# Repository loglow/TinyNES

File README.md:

# TinyNES
Classic NES games on open source hardware that fits in the palm of your hand

This work is licensed under a [Creative Commons Attribution-ShareAlike 4.0 International License](http://creativecommons.org/licenses/by-sa/4.0/).

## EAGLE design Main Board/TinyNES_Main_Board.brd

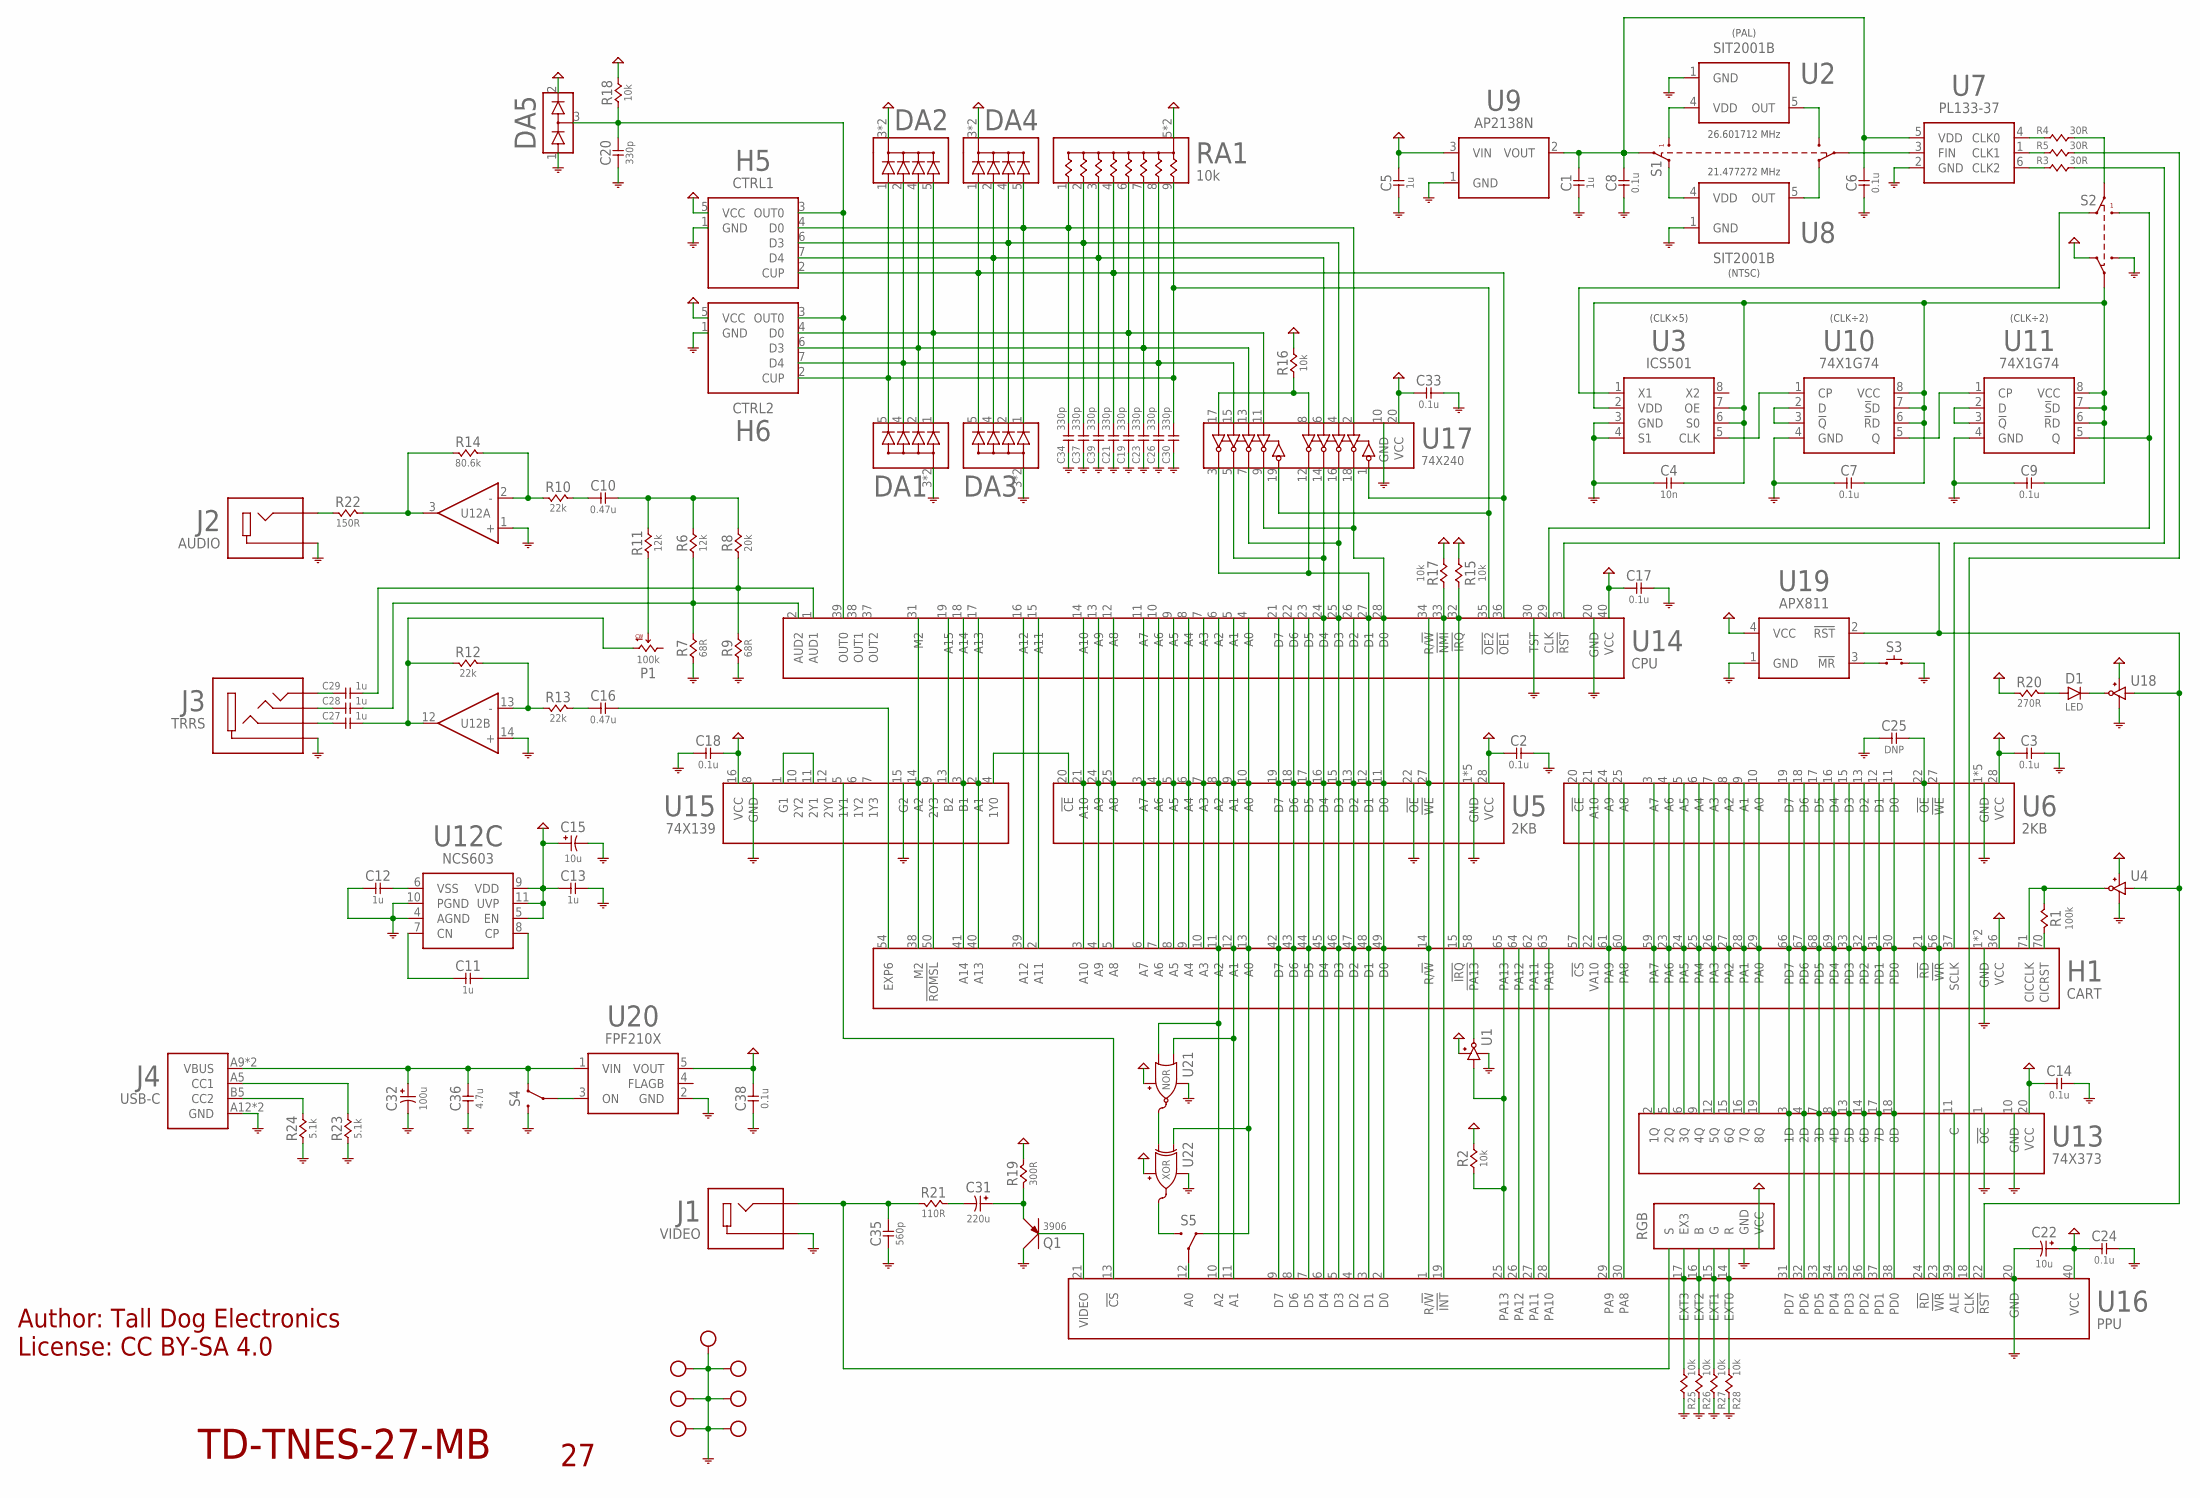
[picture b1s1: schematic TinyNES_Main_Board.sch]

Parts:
C1, C5, C11, C12, C13: 1u; 0805-NP
C2, C3, C6, C7, C8, C9, C14, C17, C18, C24, C33, C38: 0.1u; 0805-NP
C4: 10n; 0805-NP
C10, C16: 0.47u; 1206-NP
C15: 10u; ECAP-B
C19, C20, C21, C23, C26, C30, C34, C37, C39: 330p; 0805-NP
C22: 10u; 1206-P
C25: DNP; 0805-NP
C27, C28, C29: 1u; 1210-NP
C31: 220u; ECAP-E
C32: 100u; ECAP-D
C35: 560p; 0805-NP
C36: 4.7u; 0805-NP
D1: LED; LED-5MM
DA1, DA3: DA4-CA-SOT-363; SOT-363-NP
DA2, DA4: DA4-CK-SOT-363; SOT-363-NP
DA5: DA2-S; SOT-23-3
H1: CART; CART-72-2.50-CONN-VERT
H5: CTRL1; JST-PH-7
H6: CTRL2; JST-PH-7
HOLE1, HOLE2, HOLE3, HOLE4, HOLE5, HOLE6, HOLE7: HOLE-M2.5
J1: VIDEO; RCJ
J2: AUDIO; RCJ
J3: TRRS; SJ-43514
J4: USB-C; USB4125
P1: 100k; POT-3361
Q1: 3906; SOT-23-3
R1: 100k; 0805-NP
R2, R15, R16, R17, R18: 10k; 0805-NP
R3, R4, R5: 30R; 0805-NP
R6, R11: 12k; 0805-NP
R7, R9: 68R; 0805-NP
R8: 20k; 0805-NP
R10, R12, R13: 22k; 0805-NP
R14: 80.6k; 0805-NP
R19: 300R; 0805-NP
R20: 270R; 0805-NP
R21: 110R; 0805-NP
R22: 150R; 0805-NP
R23, R24: 5.1k; 0805-NP
R25, R26, R27, R28: 10k; 0603-NP
RA1: 10k; EXBA10P
RGB: RGB-TOP
S1: DPDT-LONG; JS202011J
S2: DPDT; JS202011J
S3: SWITCH; TL1105
S4: SPDT-EG1213; EG1213
S5: SPDT-CUS-12TB; CUS-12TB
U1, U4, U18: BUFFER; SOT-23-5
U2, U8: SIT2001B; SOT-23-5
U3: ICS501; SOIC-8
U5, U6: 2KB; SOIC-28
U7: PL133-37; SOT-23-6
U9: AP2138N; SOT-23-3
U10, U11: 74X1G74; TSSOP-8
U12: NCS603; TSSOP-14
U13: 74X373; SOIC-20
U14: CPU; DIP-40
U15: 74X139; SOIC-16
U16: PPU; DIP-40
U17: 74X240; SOIC-20
U19: APX811; SOT-143
U20: FPF210X; SOT-23-5
U21: NOR; SOT-23-5
U22: XOR; SOT-23-5

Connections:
1Y0-!CS: U5.20 (!CE), U15.4 (1Y0)
3V3: C1.1, C6.1, C8.1, S1.BCOM (2), U7.5 (VDD), U9.2 (VOUT)
!IRQ: H1.15 (!IRQ), R15.1, U14.32 (!IRQ)
!NMI: R17.1, U14.33 (!NMI), U16.19 (!INT)
!OE1: C21.2, DA3.5 (4), DA4.1, H5.2 (CUP), RA1.4, U14.36 (!OE1), U17.1 (1!OE)
!OE2: C30.2, DA1.5 (4), DA2.1, H6.2 (CUP), RA1.9 (8), U14.35 (!OE2), U17.19 (2!OE)
!PA13: H1.58 (!PA13), U1.4 (Y)
!ROMSEL: H1.50 (!ROMSL), U15.9 (2Y3)
A0: H1.13 (A0), S5.1, U5.10 (A0), U14.4 (A0), U22.1 (B)
A0-NOR: U21.4 (Y), U22.2 (A)
A0-PPU: S5.2, U16.12 (A0)
A0-XOR: S5.3, U22.4 (Y)
A1: H1.12 (A1), U5.9 (A1), U14.5 (A1), U16.11 (A1), U21.1 (B)
A2: H1.11 (A2), U5.8 (A2), U14.6 (A2), U16.10 (A2), U21.2 (A)
A3: H1.10 (A3), U5.7 (A3), U14.7 (A3)
A4: H1.9 (A4), U5.6 (A4), U14.8 (A4)
A5: H1.8 (A5), U5.5 (A5), U14.9 (A5)
A6: H1.7 (A6), U5.4 (A6), U14.10 (A6)
A7: H1.6 (A7), U5.3 (A7), U14.11 (A7)
A8: H1.5 (A8), U5.25 (A8), U14.12 (A8)
A9: H1.4 (A9), U5.24 (A9), U14.13 (A9)
A10: H1.3 (A10), U5.21 (A10), U14.14 (A10)
A11: H1.2 (A11), U14.15 (A11)
A12: H1.39 (A12), U14.16 (A12)
A13: H1.40 (A13), U14.17 (A13), U15.2 (A1)
A14: H1.41 (A14), U14.18 (A14), U15.3 (B1)
A15: U14.19 (A15), U15.13 (B2)
ALE: U13.11 (C), U16.39 (ALE)
AUDIO1-AC: C29.2, J3.2 (T)
AUDIO1-DC: C29.1, R8.1, R9.2, U14.1 (AUD1)
AUDIO2-AC: C28.2, J3.3 (RT)
AUDIO2-DC: C28.1, R6.1, R7.2, U14.2 (AUD2)
AUDIO-MIX: C10.2, R6.2, R8.2, R11.2
AUDIO-MIX-1: C10.1, R10.1
AUDIO-MIX-2: R10.2, R14.1, U12.2 (-)
AUDIO-MIX-AC: J2.2B (T), J2.2T (T), R22.2
AUDIO-MIX-DC: R14.2, R22.1, U12.3 (OUT)
CARTCLK: H1.37 (SCLK), R3.1
CC1: J4.A5 (CC1), R23.2
CC2: J4.B5 (CC2), R24.2
CIC: H1.71 (CICCLK), R1.2, U4.4 (Y)
CICRST: H1.70 (CICRST), R1.1
CLK0: R4.2, U7.4 (CLK0)
CLK1: R5.2, U7.1 (CLK1)
CLK2: R3.2, U7.6 (CLK2)
CLK5X: U3.5 (CLK), U10.1 (CP)
CLK5X/2: U10.5 (Q), U11.1 (CP)
CLK-FIN: S1.ACOM (5), U7.3 (FIN)
CLK-NTSC: S1.AB (6), U8.5 (OUT)
CLK-PAL: S1.AA (4), U2.5 (OUT)
CLKIN: S2.BB (3), U3.1 (X1)
CLKVCC: C4.2, C7.1, C9.1, S2.ACOM (5), U3.2 (VDD), U3.6 (S0), U3.7 (OE), U10.6 (!R!D), U10.7 (!S!D), U10.8 (VCC), U11.6 (!R!D), U11.7 (!S!D), U11.8 (VCC)
CN: C11.1, U12.7 (CN)
CP: C11.2, U12.8 (CP)
CPUCLK: S2.BA (1), U11.5 (Q), U14.29 (CLK)
CPUCLK-SW: R4.1, S2.BCOM (2)
D0: H1.49 (D0), U5.11 (D0), U14.28 (D0), U16.2 (D0), U17.9 (2Y1), U17.18 (1Y1)
D1: H1.48 (D1), U5.12 (D1), U14.27 (D1), U16.3 (D1), U17.3 (2Y4), U17.12 (1Y4)
D1-PULLUP: R16.1, U17.8 (1A4), U17.17 (2A4)
D2: H1.47 (D2), U5.13 (D2), U14.26 (D2), U16.4 (D2)
D3: H1.46 (D3), U5.15 (D3), U14.25 (D3), U16.5 (D3), U17.7 (2Y2), U17.16 (1Y2)
D4: H1.45 (D4), U5.16 (D4), U14.24 (D4), U16.6 (D4), U17.5 (2Y3), U17.14 (1Y3)
D5: H1.44 (D5), U5.17 (D5), U14.23 (D5), U16.7 (D5)
D6: H1.43 (D6), U5.18 (D6), U14.22 (D6), U16.8 (D6)
D7: H1.42 (D7), U5.19 (D7), U14.21 (D7), U16.9 (D7)
DQ1: U10.2 (D), U10.3 (!Q)
DQ2: U11.2 (D), U11.3 (!Q)
EXP6: C16.1, H1.54 (EXP6)
EXP6-1: C16.2, R13.1
EXP6-2: R12.1, R13.2, U12.13 (-)
EXP6-AC: C27.2, J3.4 (RS)
EXP6-DC: C27.1, P1.3 (CW), R12.2, U12.12 (OUT)
EXP6-MIX: P1.2 (WIPER), R11.1
EXT3: R25.2, RGB.EXT3 (EX3), U16.17 (EXT3)
G1-2Y1: U15.1 (G1), U15.11 (2Y1)
GND: C1.2, C2.2, C3.2, C4.1, C5.2, C6.2, C7.2, C8.2, C9.2, C12.1, C13.1, C14.2, C15.C, C17.2, C18.2, C19.1, C20.1, C21.1, C22.N (C), C23.1, C24.2, C25.1, C26.1, C30.1, C32.C, C33.2, C34.1, C35.1, C36.1, C37.1, C38.1, C39.1, DA1.3 (COM), DA1.6 (COM), DA3.3 (COM), DA3.6 (COM), DA5.1 (A), H1.1 (GND), H1.72 (GND), H5.1 (GND), H6.1 (GND), HOLE1.P$1, HOLE1.P$6, HOLE1.P$7, HOLE1.P$8, HOLE1.P$9, HOLE1.P$13, HOLE1.P$14, HOLE1.P$15, HOLE1.P$16, HOLE2.P$1, HOLE2.P$6, HOLE2.P$7, HOLE2.P$8, HOLE2.P$9, HOLE2.P$13, HOLE2.P$14, HOLE2.P$15, HOLE2.P$16, HOLE3.P$1, HOLE3.P$6, HOLE3.P$7, HOLE3.P$8, HOLE3.P$9, HOLE3.P$13, HOLE3.P$14, HOLE3.P$15, HOLE3.P$16, HOLE4.P$1, HOLE4.P$6, HOLE4.P$7, HOLE4.P$8, HOLE4.P$9, HOLE4.P$13, HOLE4.P$14, HOLE4.P$15, HOLE4.P$16, HOLE5.P$1, HOLE5.P$6, HOLE5.P$7, HOLE5.P$8, HOLE5.P$9, HOLE5.P$13, HOLE5.P$14, HOLE5.P$15, HOLE5.P$16, HOLE6.P$1, HOLE6.P$6, HOLE6.P$7, HOLE6.P$8, HOLE6.P$9, HOLE6.P$13, HOLE6.P$14, HOLE6.P$15, HOLE6.P$16, HOLE7.P$1, HOLE7.P$6, HOLE7.P$7, HOLE7.P$8, HOLE7.P$9, HOLE7.P$13, HOLE7.P$14, HOLE7.P$15, HOLE7.P$16, J1.1B (S), J1.1T (S), J2.1B (S), J2.1T (S), J3.1 (S), J4.A12 (GND), J4.B12 (GND), Q1.3 (C), R7.1, R9.1, R23.1, R24.1, R25.1, R26.1, R27.1, R28.1, RGB.GND, S2.AA (4), S3.2, S4.3, U1.1 (GND), U1.3 (GND), U2.1 (GND), U3.3 (GND), U3.4 (S1), U4.1 (GND), U4.3 (GND), U5.1 (GND), U5.2 (GND), U5.14 (GND), U5.22 (!OE), U5.23 (GND), U5.26 (GND), U6.1 (GND), U6.2 (GND), U6.14 (GND), U6.23 (GND), U6.26 (GND), U7.2 (GND), U8.1 (GND), U9.1 (GND), U10.4 (GND), U11.4 (GND), U12.1 (+), U12.4 (AGND), U12.10 (PGND), U12.14 (+), U13.1 (!OC), U13.10 (GND), U14.20 (GND), U14.30 (TST), U15.8 (GND), U15.15 (G2), U16.20 (GND), U17.10 (GND), U18.1 (GND), U18.3 (GND), U19.1 (GND), U20.2 (GND), U21.3 (GND), U22.3 (GND)
GND-CAP: C12.2, U12.6 (VSS)
LEDA: D1.A, R20.1
LEDK: D1.K (C), U18.4 (Y)
M2: H1.38 (M2), U14.31 (M2), U15.14 (A2)
OUT0: C20.2, DA5.3 (COM), H5.3 (OUT0), H6.3 (OUT0), R18.1, U14.39 (OUT0)
P1-D0: C34.2, DA3.1, DA4.5 (4), H5.4 (D0), RA1.1, U17.2 (1A1)
P1-D3: C37.2, DA3.2, DA4.4 (3), H5.6 (D3), RA1.2, U17.4 (1A2)
P1-D4: C39.2, DA3.4 (3), DA4.2, H5.7 (D4), RA1.3, U17.6 (1A3)
P2-D0: C19.2, DA1.1, DA2.5 (4), H6.4 (D0), RA1.6 (5), U17.11 (2A1)
P2-D3: C23.2, DA1.2, DA2.4 (3), H6.6 (D3), RA1.7 (6), U17.13 (2A2)
P2-D4: C26.2, DA1.4 (3), DA2.2, H6.7 (D4), RA1.8 (7), U17.15 (2A3)
PA0: H1.29 (PA0), U6.10 (A0), U13.19 (8Q)
PA1: H1.28 (PA1), U6.9 (A1), U13.16 (7Q)
PA2: H1.27 (PA2), U6.8 (A2), U13.15 (6Q)
PA3: H1.26 (PA3), U6.7 (A3), U13.12 (5Q)
PA4: H1.25 (PA4), U6.6 (A4), U13.9 (4Q)
PA5: H1.24 (PA5), U6.5 (A5), U13.6 (3Q)
PA6: H1.23 (PA6), U6.4 (A6), U13.5 (2Q)
PA7: H1.59 (PA7), U6.3 (A7), U13.2 (1Q)
PA8: H1.60 (PA8), U6.25 (A8), U16.30 (PA8)
PA9: H1.61 (PA9), U6.24 (A9), U16.29 (PA9)
PA10: H1.63 (PA10), U16.28 (PA10)
PA11: H1.62 (PA11), U16.27 (PA11)
PA12: H1.64 (PA12), U16.26 (PA12)
PA13: H1.65 (PA13), R2.1, U1.2 (A), U16.25 (PA13)
PD0: H1.30 (PD0), U6.11 (D0), U13.18 (8D), U16.38 (PD0)
PD1: H1.31 (PD1), U6.12 (D1), U13.17 (7D), U16.37 (PD1)
PD2: H1.32 (PD2), U6.13 (D2), U13.14 (6D), U16.36 (PD2)
PD3: H1.33 (PD3), U6.15 (D3), U13.13 (5D), U16.35 (PD3)
PD4: H1.69 (PD4), U6.16 (D4), U13.8 (4D), U16.34 (PD4)
PD5: H1.68 (PD5), U6.17 (D5), U13.7 (3D), U16.33 (PD5)
PD6: H1.67 (PD6), U6.18 (D6), U13.4 (2D), U16.32 (PD6)
PD7: H1.66 (PD7), U6.19 (D7), U13.3 (1D), U16.31 (PD7)
PPU-!CS: U15.5 (1Y1), U16.13 (!CS)
PPU-!RD: C25.2, H1.21 (!RD), U6.22 (!OE), U16.24 (!RD)
PPU-!WR: H1.56 (!WR), U6.27 (!WE), U16.23 (!WR)
PPUCLK: R5.1, U16.18 (CLK)
PWR-ON: S4.2, U20.3 (ON)
R/!W: H1.14 (R/!W), U5.27 (!WE), U14.34 (R/!W), U16.1 (R/!W)
RESET: U4.2 (A), U14.3 (!RST), U16.22 (!RST), U18.2 (A), U19.2 (!RST)
RESET-SW: S3.1, U19.3 (!MR)
RGB-BLUE: R26.2, RGB.B, U16.16 (EXT2)
RGB-GREEN: R27.2, RGB.G, U16.15 (EXT1)
RGB-RED: R28.2, RGB.R, U16.14 (EXT0)
VCC: C2.1, C3.1, C5.1, C13.2, C14.1, C15.A, C17.1, C18.1, C22.P (A), C24.1, C33.1, C38.2, DA2.3 (COM), DA2.6 (COM), DA4.3 (COM), DA4.6 (COM), DA5.2 (K), H1.36 (VCC), H5.5 (VCC), H6.5 (VCC), R2.2, R15.2, R16.2, R17.2, R18.2, R19.1, R20.2, RA1.5 (COM), RA1.10 (COM), RGB.VCC@1 (VCC), RGB.VCC@2 (VCC), RGB.VCC@3 (VCC), S2.AB (6), U1.5 (VCC), U4.5 (VCC), U5.28 (VCC), U6.28 (VCC), U9.3 (VIN), U12.5 (EN), U12.9 (VDD), U12.11 (UVP), U13.20 (VCC), U14.40 (VCC), U15.16 (VCC), U16.40 (VCC), U17.20 (VCC), U18.5 (VCC), U19.4 (VCC), U20.5 (VOUT), U21.5 (VCC), U22.5 (VCC)
VDD-NTSC: S1.BB (3), U8.4 (VDD)
VDD-PAL: S1.BA (1), U2.4 (VDD)
VIDEO: Q1.1 (B), U16.21 (VIDEO)
VIDEO1: C31.A, Q1.2 (E), R19.2
VIDEO2: C31.C, R21.1
VIDEO-OUT: C35.2, J1.2B (T), J1.2T (T), R21.2, RGB.S
VIN: C32.A, C36.2, J4.A9 (VBUS), J4.B9 (VBUS), S4.1, U20.1 (VIN)
VRAM-!CS: H1.57 (!CS), U6.20 (!CE)
VRAM-A10: H1.22 (VA10), U6.21 (A10)

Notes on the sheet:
TD-TNES-27-MB
Author: Tall Dog Electronics License: CC BY-SA 4.0
21.477272 MHz
26.601712 MHz
(CLK×5)
(CLK÷2)
(NTSC)
(PAL)

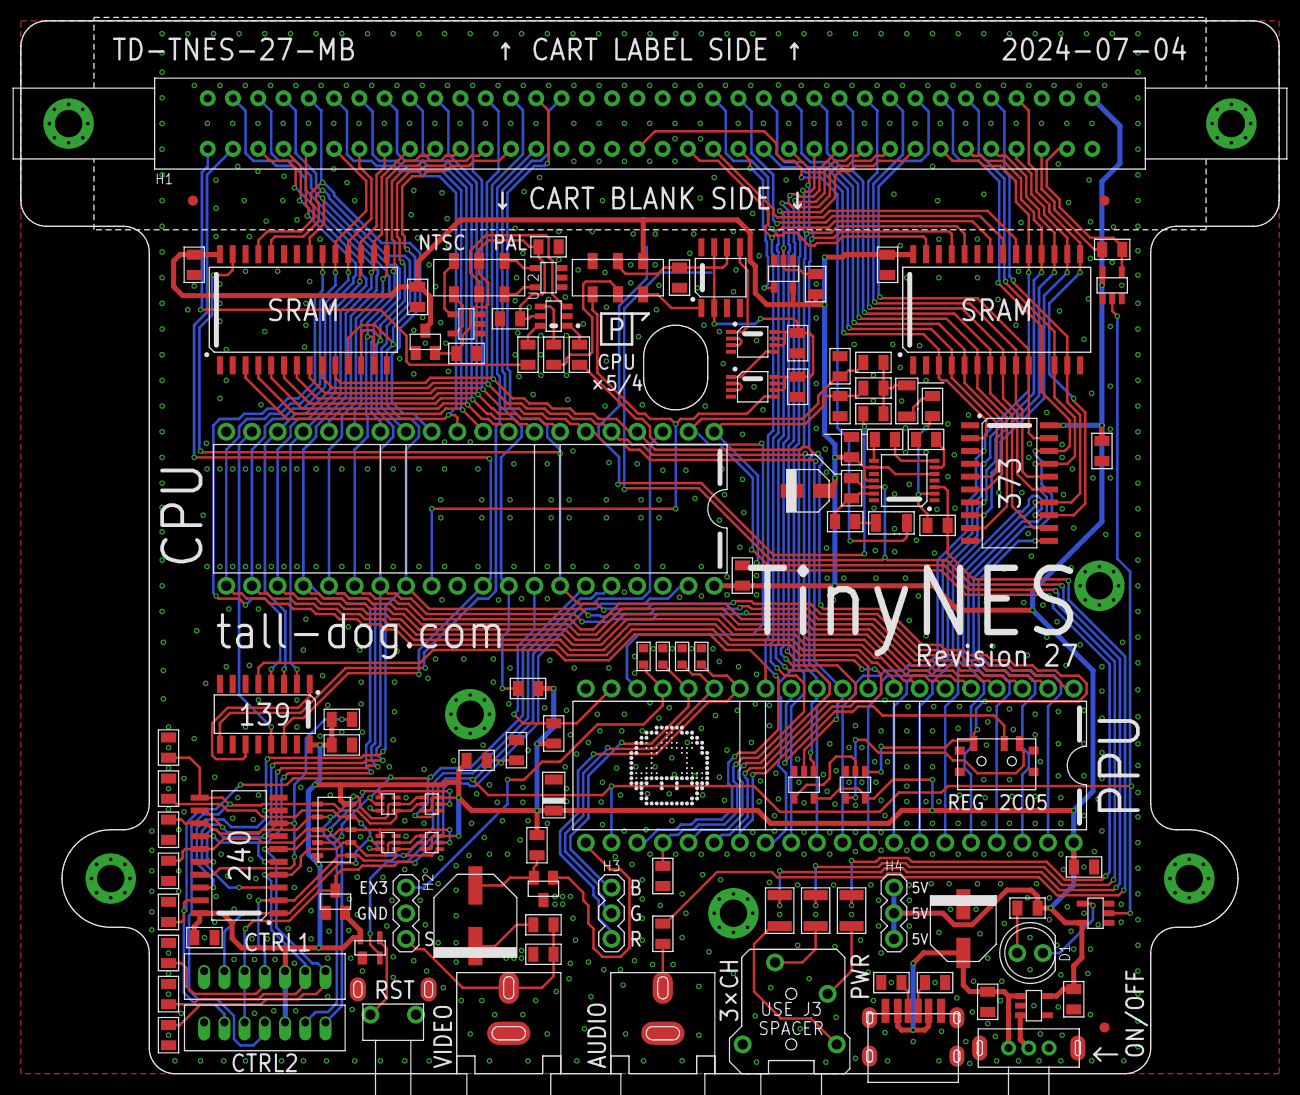
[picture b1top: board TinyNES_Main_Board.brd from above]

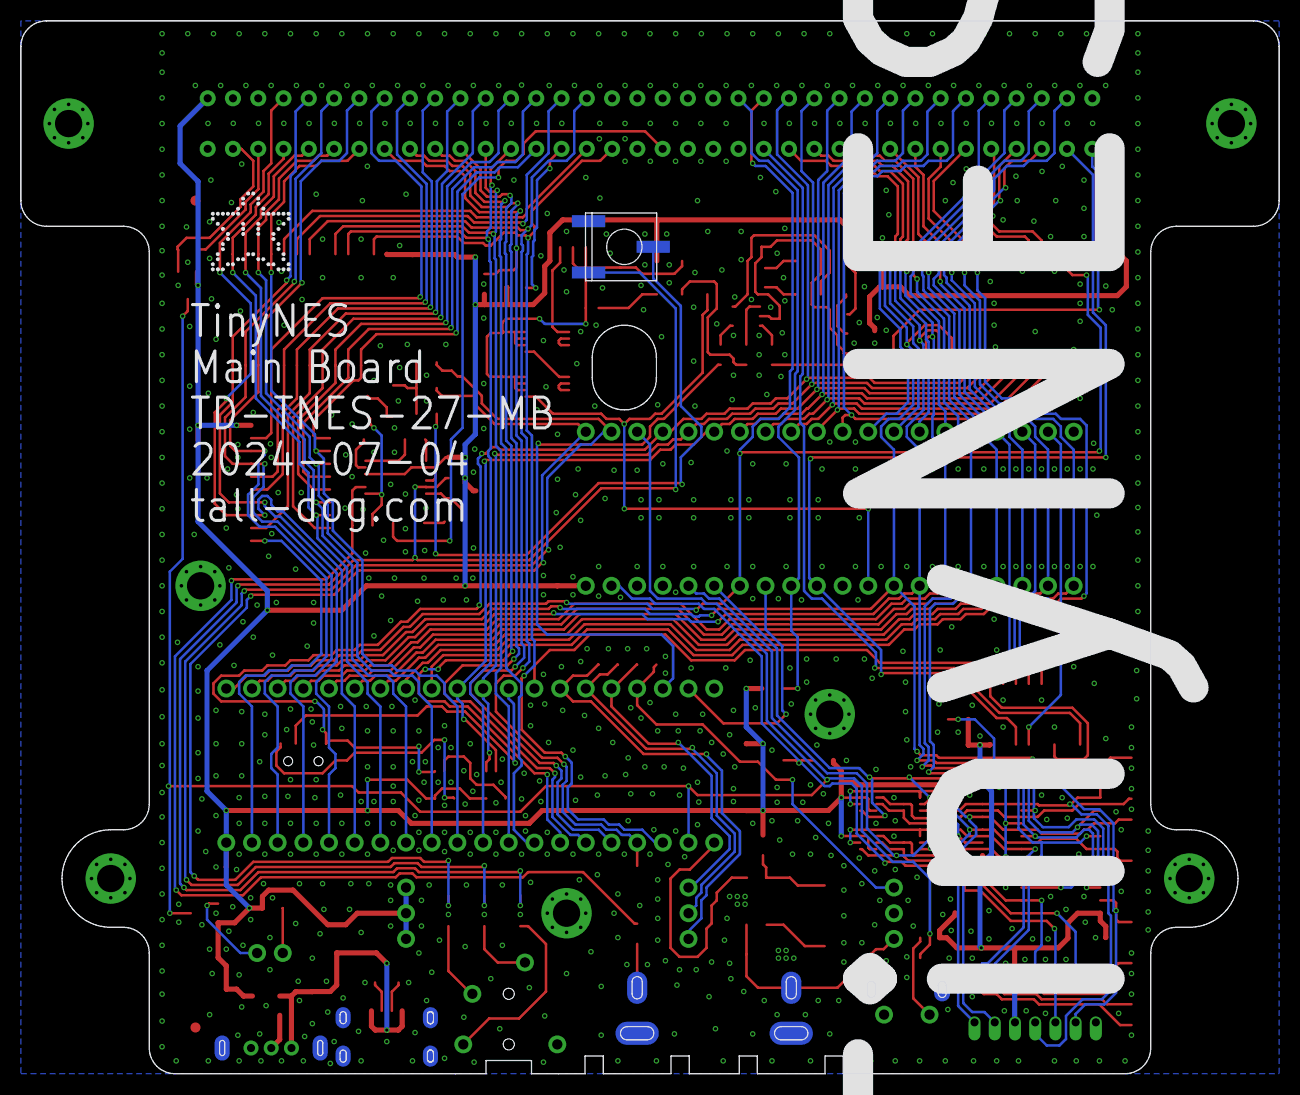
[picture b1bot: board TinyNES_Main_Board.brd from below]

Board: 2 copper layers, 124.5 x 104.1 mm, 124 parts (2 on the bottom side), 130 nets.

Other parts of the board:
FICUCIAL1, FICUCIAL2, FICUCIAL3: FICUCIAL; FIDUCIAL
STAR: STAR; _PIXEL-ART-STAR
U$1: _PIXEL-ART-1UP
U$2: _PIXEL-ART-LEAF

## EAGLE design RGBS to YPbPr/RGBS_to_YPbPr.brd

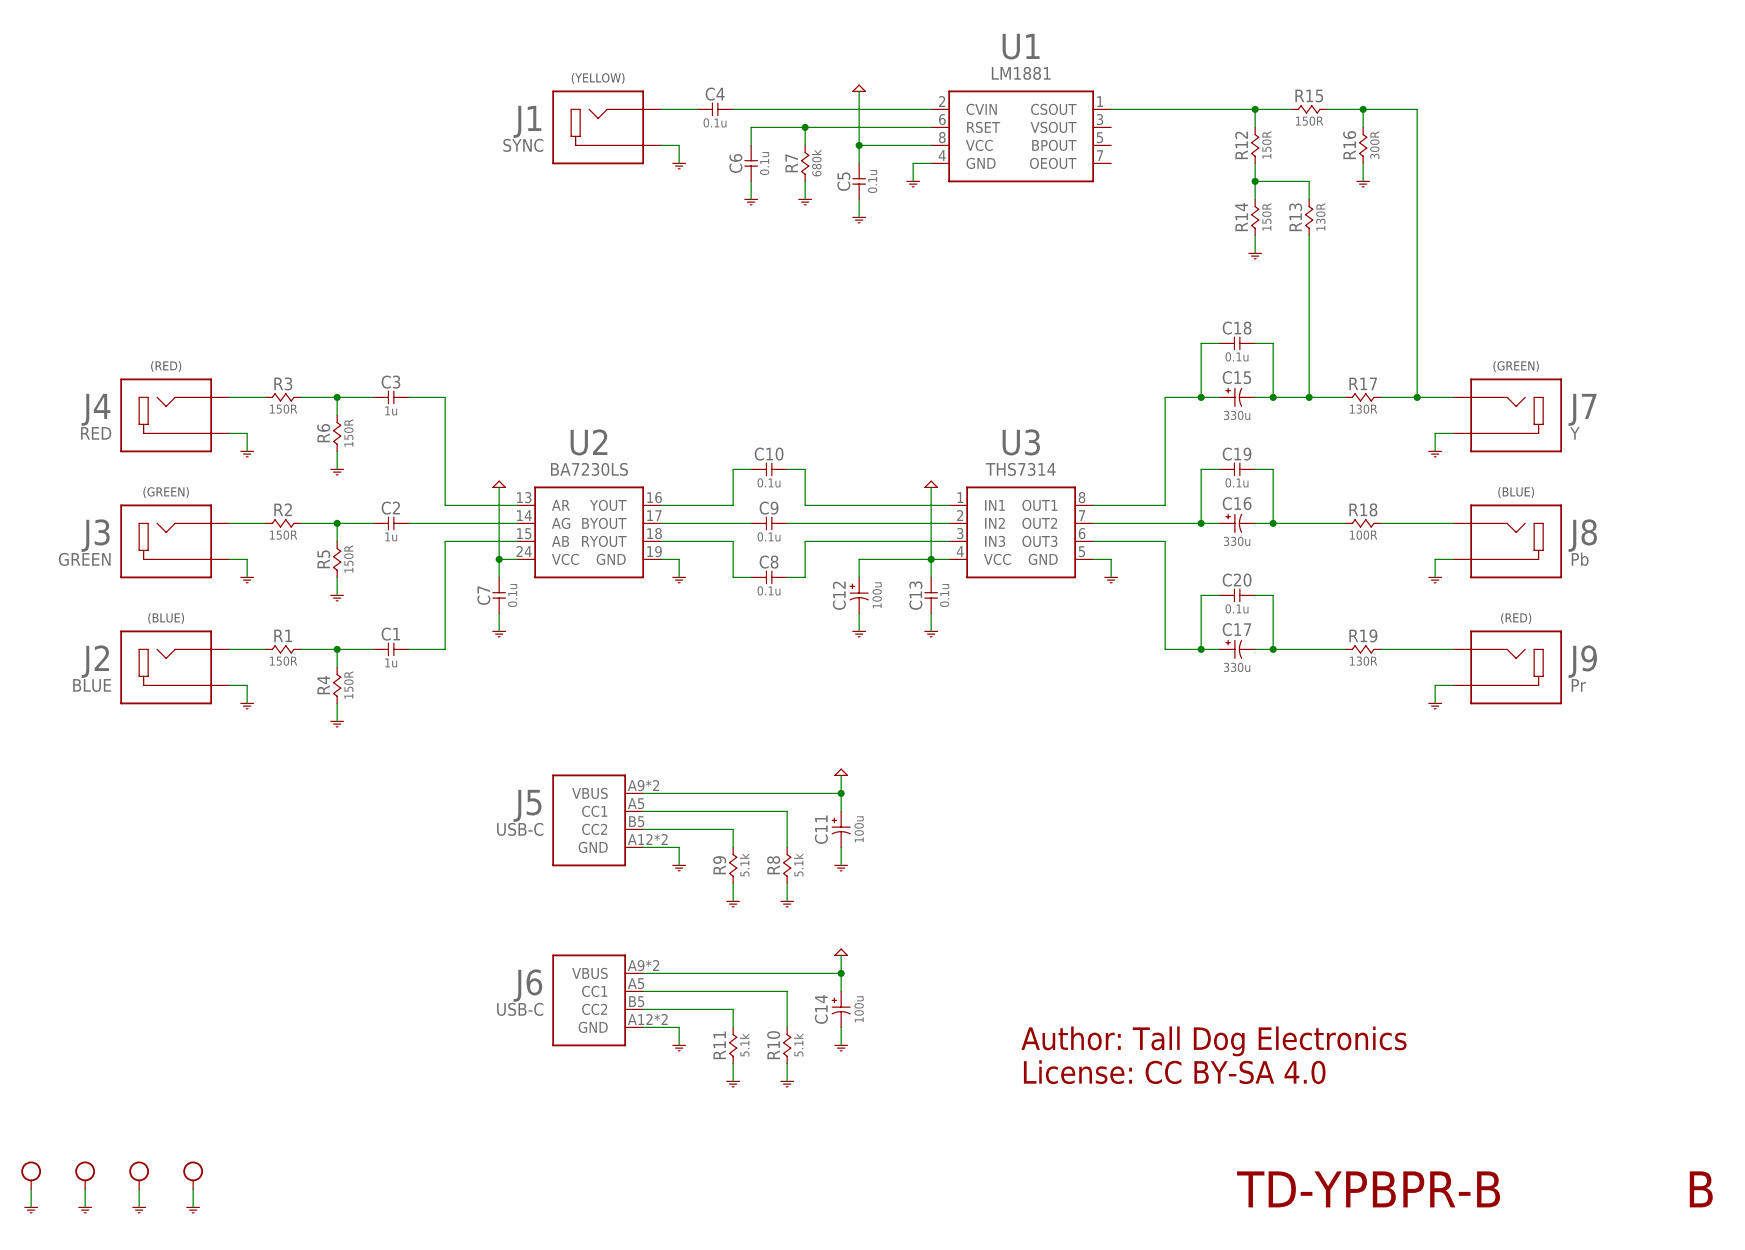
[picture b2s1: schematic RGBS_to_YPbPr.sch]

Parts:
C1, C2, C3: 1u; 0805-NP
C4, C5, C6, C7, C8, C9, C10, C13, C18, C19, C20: 0.1u; 0805-NP
C11, C12, C14: 100u; ECAP-D
C15, C16, C17: 330u; ECAP-E
HOLE1, HOLE2, HOLE3, HOLE4: HOLE-M2.5
J1: SYNC; RCJ
J2: BLUE; RCJ
J3: GREEN; RCJ
J4: RED; RCJ
J5, J6: USB-C; USB4125
J7: Y; RCJ
J8: Pb; RCJ
J9: Pr; RCJ
R1, R2, R3, R4, R5, R6, R12, R14, R15: 150R; 0805-NP
R7: 680k; 0805-NP
R8, R9, R10, R11: 5.1k; 0805-NP
R13, R17, R19: 130R; 0805-NP
R16: 300R; 0805-NP
R18: 100R; 0805-NP
U1: LM1881; SOIC-8
U2: BA7230LS; SZIP-24
U3: THS7314; SOIC-8

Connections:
BLUE: C1.1, R1.2, R4.2
GND: C5.1, C6.1, C7.1, C11.C, C12.C, C13.1, C14.C, HOLE1.P$1, HOLE1.P$6, HOLE1.P$7, HOLE1.P$8, HOLE1.P$9, HOLE1.P$13, HOLE1.P$14, HOLE1.P$15, HOLE1.P$16, HOLE2.P$1, HOLE2.P$6, HOLE2.P$7, HOLE2.P$8, HOLE2.P$9, HOLE2.P$13, HOLE2.P$14, HOLE2.P$15, HOLE2.P$16, HOLE3.P$1, HOLE3.P$6, HOLE3.P$7, HOLE3.P$8, HOLE3.P$9, HOLE3.P$13, HOLE3.P$14, HOLE3.P$15, HOLE3.P$16, HOLE4.P$1, HOLE4.P$6, HOLE4.P$7, HOLE4.P$8, HOLE4.P$9, HOLE4.P$13, HOLE4.P$14, HOLE4.P$15, HOLE4.P$16, J1.1B (S), J1.1T (S), J2.1B (S), J2.1T (S), J3.1B (S), J3.1T (S), J4.1B (S), J4.1T (S), J5.A12 (GND), J5.B12 (GND), J6.A12 (GND), J6.B12 (GND), J7.1B (S), J7.1T (S), J8.1B (S), J8.1T (S), J9.1B (S), J9.1T (S), R4.1, R5.1, R6.1, R7.1, R8.1, R9.1, R10.1, R11.1, R14.1, R16.1, U1.4 (GND), U2.19 (GND), U3.5 (GND)
GREEN: C2.1, R2.2, R5.2
unnamed: J7.2B (T), J7.2T (T), R15.2, R16.2, R17.2
unnamed: C16.C, C19.2, R18.1
unnamed: C16.A, C19.1, U3.7 (OUT2)
unnamed: C15.A, C18.1, U3.8 (OUT1)
unnamed: C17.C, C20.2, R19.1
unnamed: C17.A, C20.1, U3.6 (OUT3)
unnamed: C4.2, U1.2 (CVIN)
unnamed: C10.2, U3.1 (IN1)
unnamed: C9.2, U3.2 (IN2)
unnamed: C8.2, U3.3 (IN3)
unnamed: J6.B5 (CC2), R11.2
unnamed: J6.A5 (CC1), R10.2
unnamed: J5.B5 (CC2), R9.2
unnamed: J5.A5 (CC1), R8.2
unnamed: C8.1, U2.18 (RYOUT)
unnamed: J4.2B (T), J4.2T (T), R3.1
unnamed: J3.2B (T), J3.2T (T), R2.1
unnamed: C15.C, C18.2, R13.1, R17.1
unnamed: C9.1, U2.17 (BYOUT)
unnamed: J2.2B (T), J2.2T (T), R1.1
unnamed: C10.1, U2.16 (YOUT)
unnamed: R12.1, R13.2, R14.2
unnamed: C3.2, U2.13 (AR)
unnamed: C2.2, U2.14 (AG)
unnamed: C1.2, U2.15 (AB)
unnamed: C6.2, R7.2, U1.6 (RSET)
PB: J8.2B (T), J8.2T (T), R18.2
PR: J9.2B (T), J9.2T (T), R19.2
RED: C3.1, R3.2, R6.2
SYNC: C4.1, J1.2B (T), J1.2T (T)
VCC: C5.2, C7.2, C11.A, C12.A, C13.2, C14.A, J5.A9 (VBUS), J5.B9 (VBUS), J6.A9 (VBUS), J6.B9 (VBUS), U1.8 (VCC), U2.24 (VCC), U3.4 (VCC)
Y: R12.2, R15.1, U1.1 (CSOUT)

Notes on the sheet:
TD-YPBPR-B
Author: Tall Dog Electronics License: CC BY-SA 4.0
(RED)
(GREEN)
(BLUE)
(YELLOW)

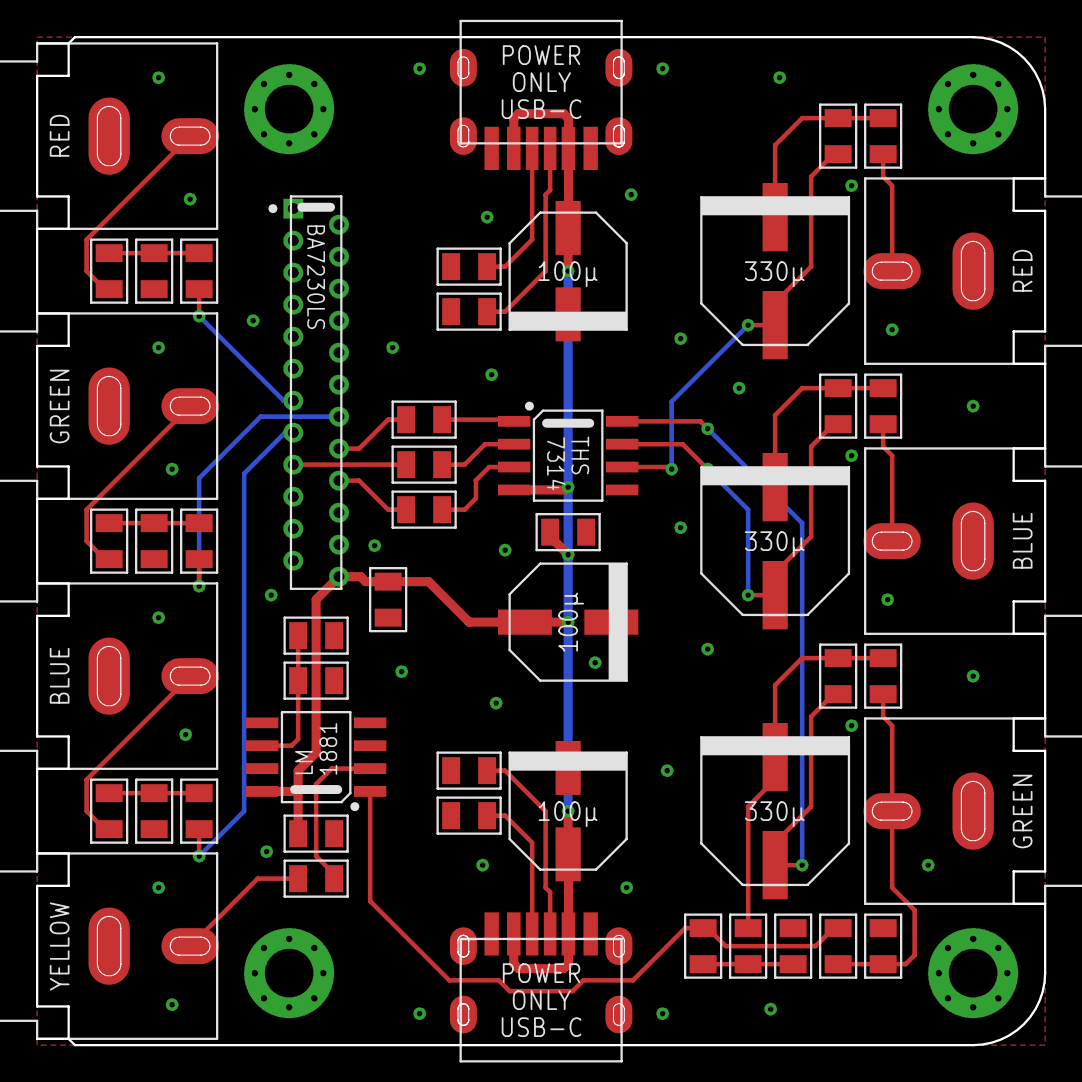
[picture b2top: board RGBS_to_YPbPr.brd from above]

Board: 2 copper layers, 56.0 x 56.0 mm, 55 parts (0 on the bottom side), 35 nets.

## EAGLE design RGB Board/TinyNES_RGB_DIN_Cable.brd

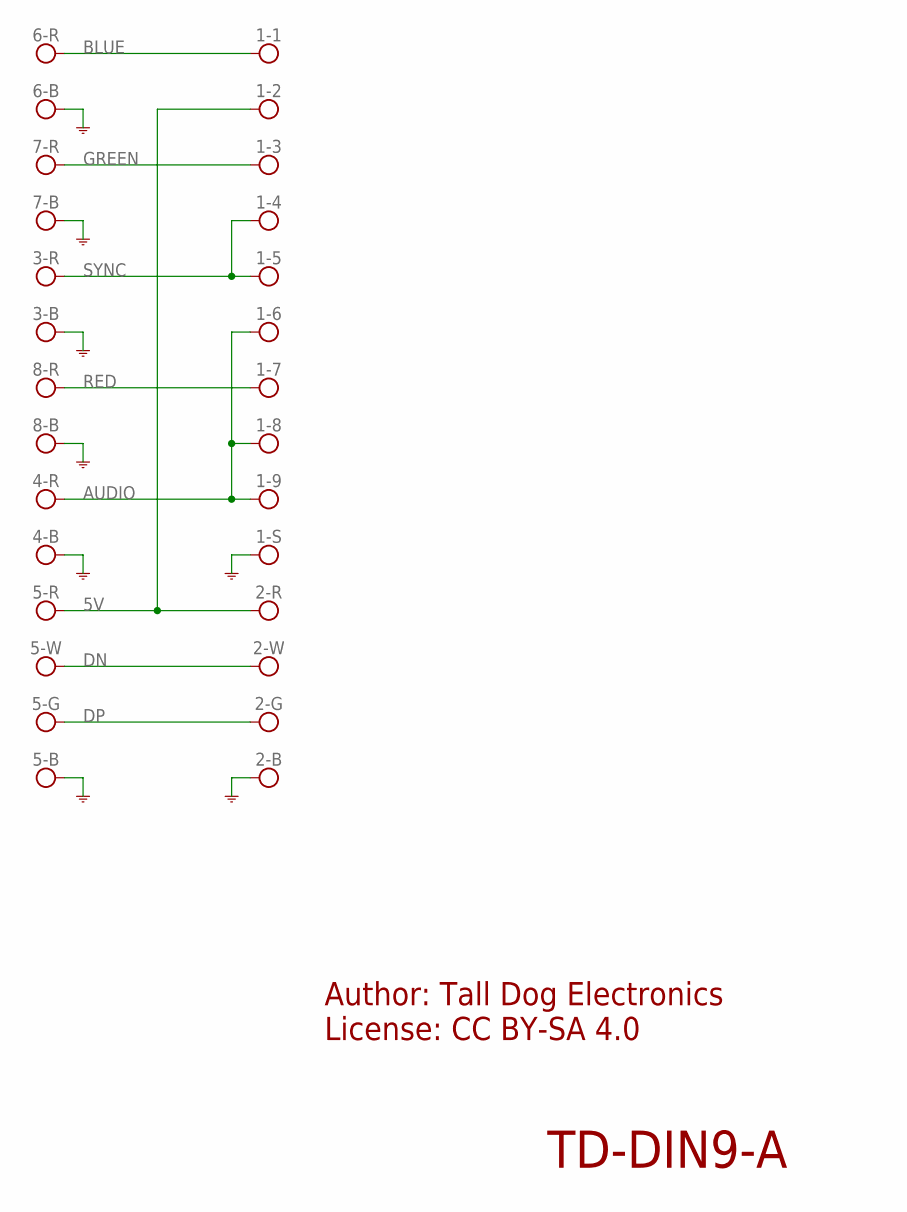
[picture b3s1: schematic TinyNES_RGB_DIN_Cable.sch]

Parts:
1-1, 1-2, 1-3, 1-4, 1-5, 1-6, 1-7, 1-8, 1-9, 1-S, 2-B, 2-G, 2-R, 2-W, 3-B, 3-R, 4-B, 4-R, 5-B, 5-G, 5-R, 5-W, 6-B, 6-R, 7-B, 7-R, 8-B, 8-R: HOLE-CABLE-PAD; CABLE-PAD

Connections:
5V: 1-2.P, 2-R.P, 5-R.P
AUDIO: 1-6.P, 1-8.P, 1-9.P, 4-R.P
BLUE: 1-1.P, 6-R.P
DN: 2-W.P, 5-W.P
DP: 2-G.P, 5-G.P
GND: 1-S.P, 2-B.P, 3-B.P, 4-B.P, 5-B.P, 6-B.P, 7-B.P, 8-B.P
GREEN: 1-3.P, 7-R.P
RED: 1-7.P, 8-R.P
SYNC: 1-4.P, 1-5.P, 3-R.P

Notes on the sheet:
TD-DIN9-A
Author: Tall Dog Electronics License: CC BY-SA 4.0

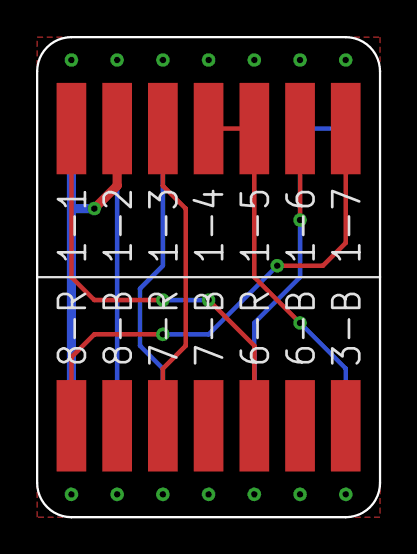
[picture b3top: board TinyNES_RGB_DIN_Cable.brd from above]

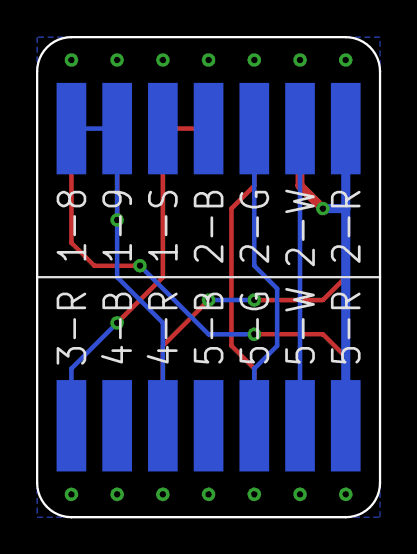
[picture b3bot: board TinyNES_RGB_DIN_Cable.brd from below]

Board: 2 copper layers, 19.1 x 26.7 mm, 28 parts (14 on the bottom side), 9 nets.

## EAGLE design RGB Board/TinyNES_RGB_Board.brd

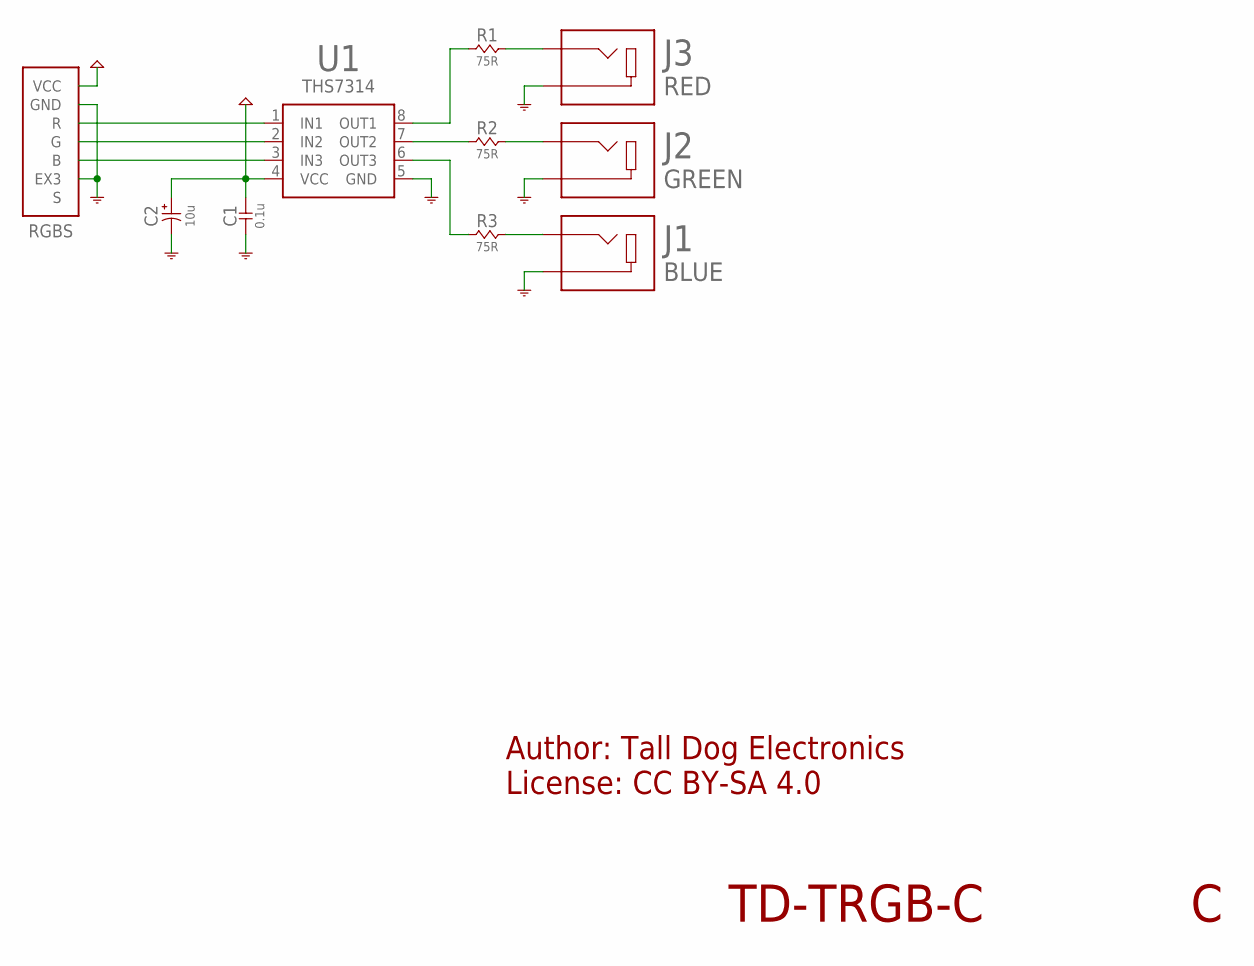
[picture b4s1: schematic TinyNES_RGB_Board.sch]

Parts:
C1: 0.1u; 0805-NP
C2: 10u; 1206-P
J1: BLUE; RCJ-VERT
J2: GREEN; RCJ-VERT
J3: RED; RCJ-VERT
R1, R2, R3: 75R; 0805-NP
RGBS: RGB-BOT
U1: THS7314; SOIC-8

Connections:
GND: C1.2, C2.N (C), J1.1 (S), J1.3 (S), J2.1 (S), J2.3 (S), J3.1 (S), J3.3 (S), RGBS.EXT3 (EX3), RGBS.GND, U1.5 (GND)
unnamed: RGBS.R, U1.1 (IN1)
unnamed: R3.1, U1.6 (OUT3)
unnamed: J3.2 (T), R1.2
unnamed: R1.1, U1.8 (OUT1)
unnamed: RGBS.G, U1.2 (IN2)
unnamed: RGBS.B, U1.3 (IN3)
unnamed: J2.2 (T), R2.2
unnamed: R2.1, U1.7 (OUT2)
unnamed: J1.2 (T), R3.2
VCC: C1.1, C2.P (A), RGBS.VCC@1 (VCC), RGBS.VCC@2 (VCC), RGBS.VCC@3 (VCC), U1.4 (VCC)

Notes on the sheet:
TD-TRGB-C
Author: Tall Dog Electronics License: CC BY-SA 4.0

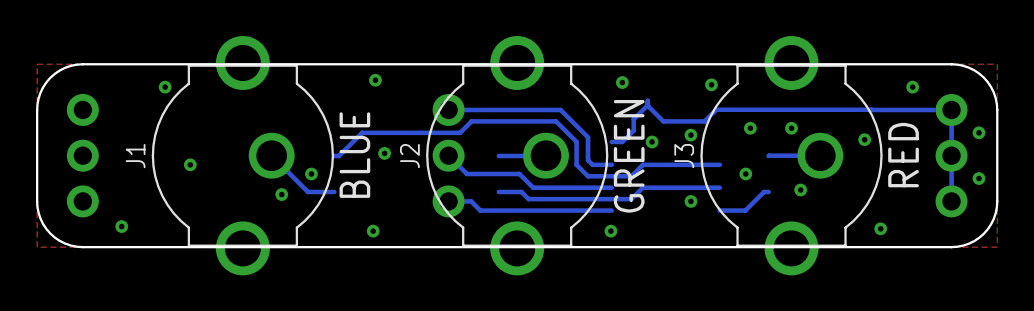
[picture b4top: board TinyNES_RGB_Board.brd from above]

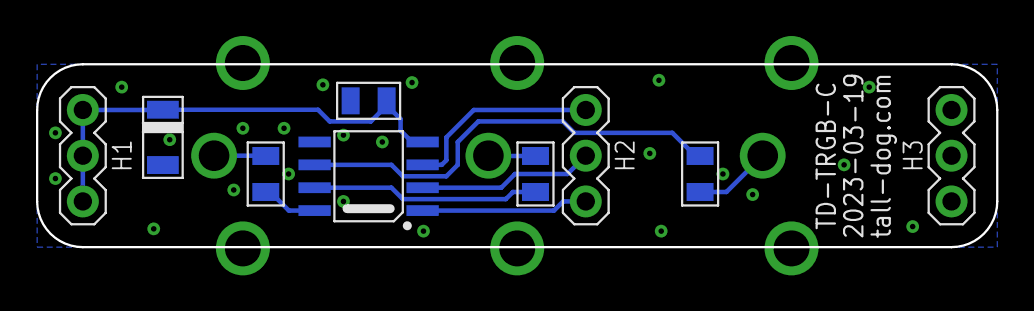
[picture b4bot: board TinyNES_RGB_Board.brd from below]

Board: 2 copper layers, 53.3 x 10.2 mm, 10 parts (6 on the bottom side), 11 nets.
